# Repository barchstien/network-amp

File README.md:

# network-amp
PCB including DAC, audio amp, RaspberryPi interface and power supply

<br /><span xmlns:dct="http://purl.org/dc/terms/" property="dct:title">network-amp</span> by <span xmlns:cc="http://creativecommons.org/ns#" property="cc:attributionName">bastienauneau</span> is licensed under a <a rel="license" href="http://creativecommons.org/licenses/by-sa/4.0/">Creative Commons Attribution-ShareAlike 4.0 International License</a>.

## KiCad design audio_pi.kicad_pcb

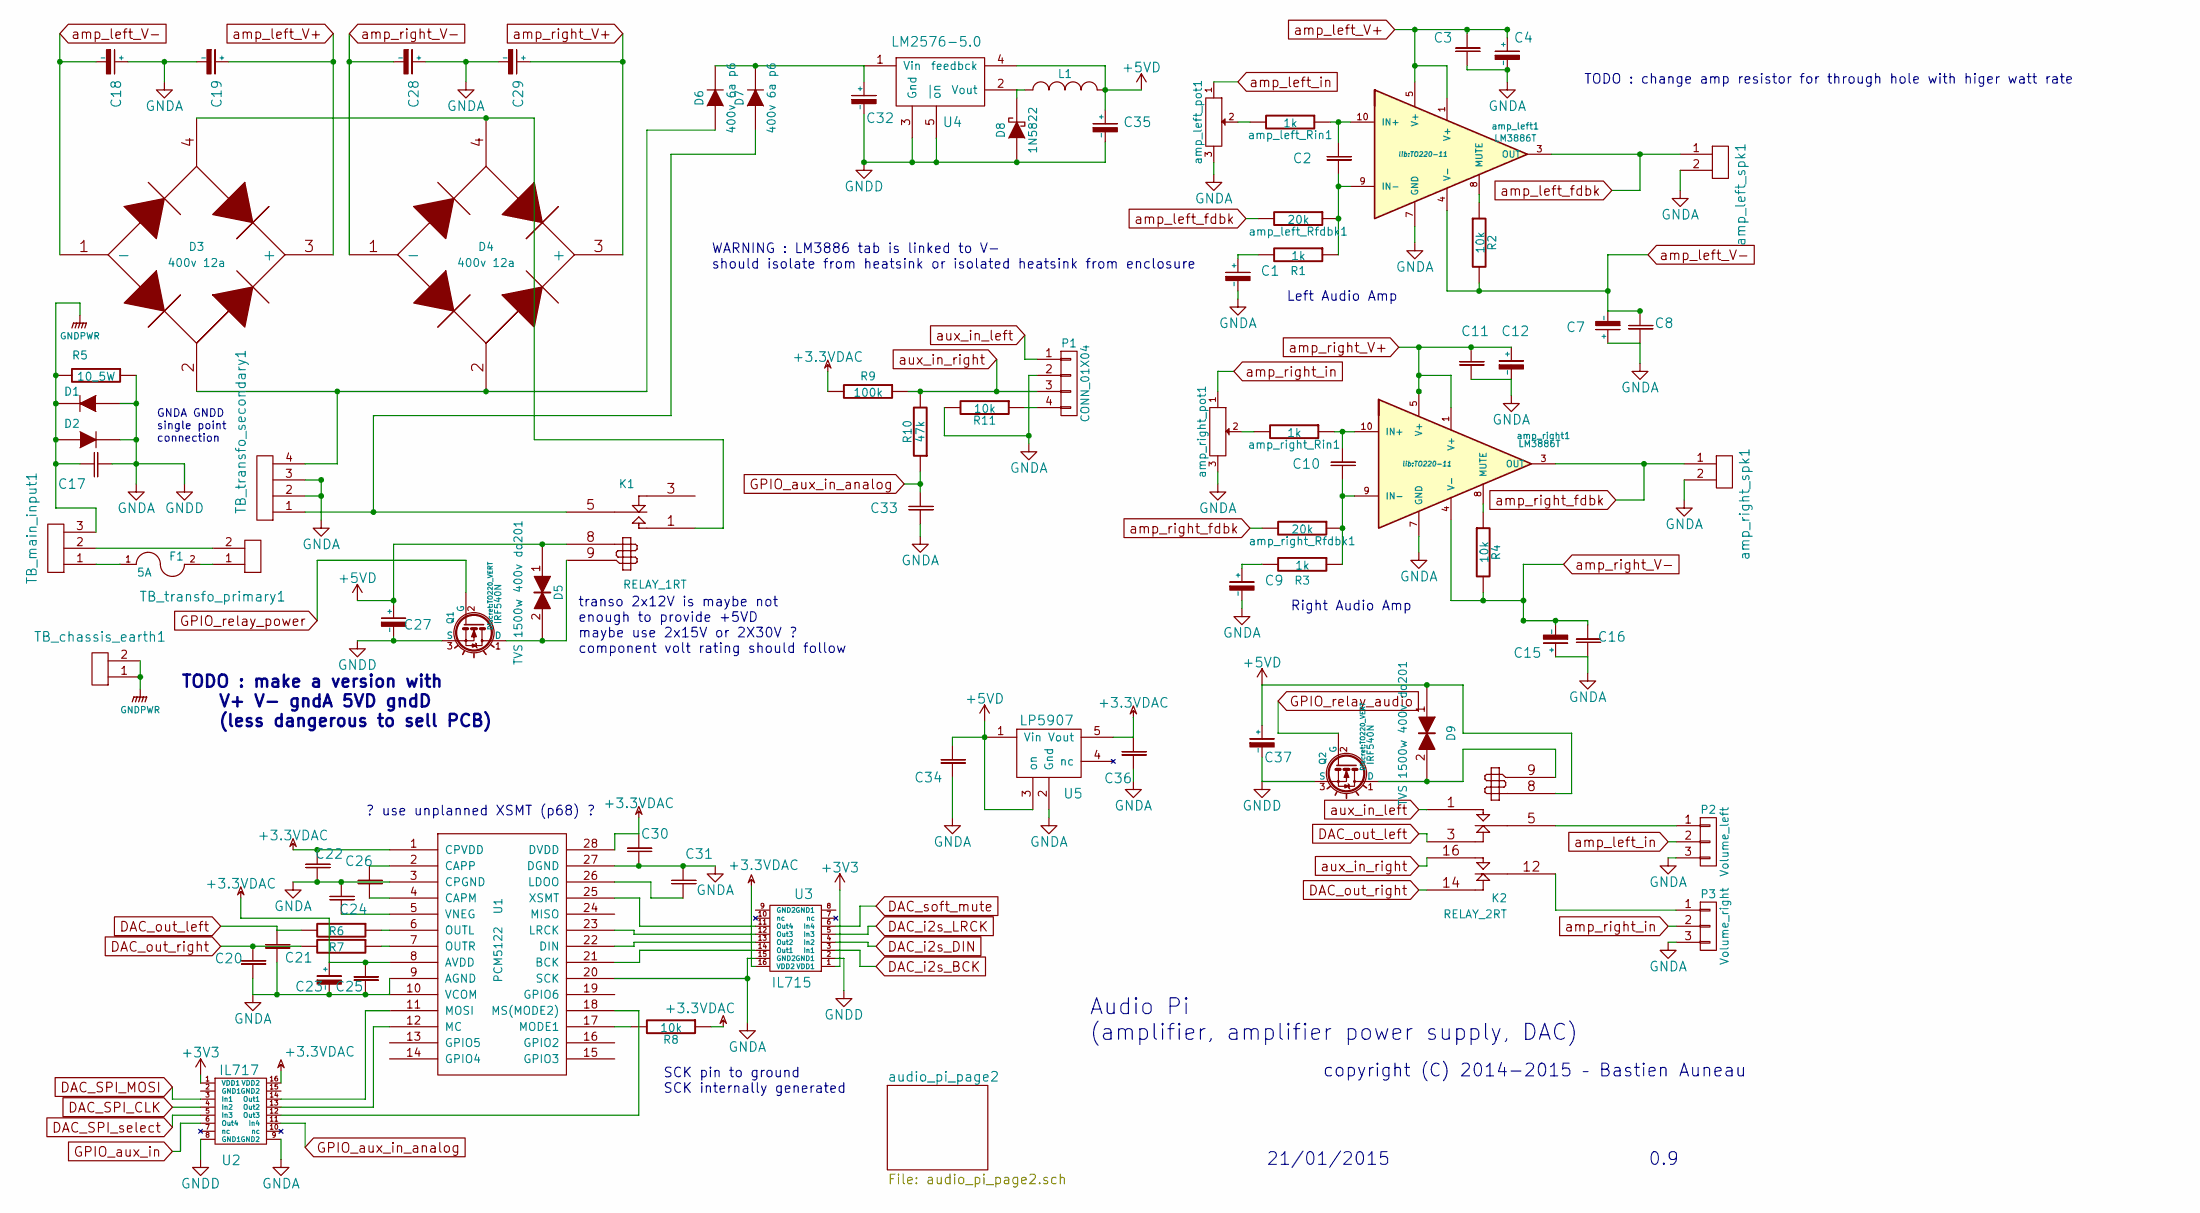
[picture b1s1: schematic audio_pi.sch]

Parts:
C1, C9: 22uf; Capacitor8x13RM3.8
C2, C10: 220pf; Capacitor6MMDiscRM5
C3, C8, C11, C16, C17: 100nf; Capacitor6MMDiscRM5
C4, C7, C12, C15, C23: 10uf; C1V7
C18, C19, C28, C29: 4700uF; Capacitor26x45RM10
C20, C21: 2.2nf; C_1206
C22, C25, C30, C31: 0.1uf; C_1206
C24, C26: 2.2uf; C_1206
C27, C32, C37: 100uf; Capacitor10x21RM5
C33: 10nf; C_1206
C34, C36: 1uf; C_1206
C35: 2200uf; Capacitor16x25RM7.5
D1, D2: 400v 6a p6; Diode_P600_Vertical_KathodeUp
D3, D4: 400v 12a; bornier4
D5, D9: TVS 1500w 400v do201; Diode_DO-41_SOD81_Horizontal_RM10
D6, D7: 400v 6a p6; Diode_P600_Horizontal
D8: 1N5822; Diode_DO-41_SOD81_Vertical_KathodeUp
F1: 5A; Fuseholder5x20_horiz_SemiClosed_Casing10x25mm
K1: RELAY_1RT; Relay_Power
K2: RELAY_2RT; Relais_double
L1: 100uH 5A; inductance
P1: CONN_01X04; Pin_Header_Straight_1x04
P2: Volume_left; Pin_Header_Straight_1x03
P3: Volume_right; Pin_Header_Straight_1x03
Q1, Q2: IRF540N; TO220_VERT
R1, R3: 1k; Resistor_Horizontal_RM10mm
R2, R4: 10k; Resistor_Horizontal_RM10mm
R5: 10_5W; Resistor_Horizontal_RM25mm
R6, R7: 470R; R_1206
R8, R11: 10k; R_1206
R9: 100k; R_1206
R10: 47k; R_1206
TB_chassis_earth1: Terminal_block_2; AK300-2
TB_main_input1: Terminal_block_3; AK300-3
TB_transfo_primary1: Terminal_block_2; AK300-2
TB_transfo_secondary1: Terminal_block_4; AK300-4
U1: PCM5122; TSSOP-28_4.4x9.7mm_Pitch0.65mm
U2: IL717; SOIC-16_3.9x9.9mm_Pitch1.27mm
U3: IL715; SOIC-16_3.9x9.9mm_Pitch1.27mm
U4: LM2576-5.0; Pentawatt_Neutral_Staggered_Verical_TO220-5-T05D
U5: LP5907; SOT-23-5
amp_left1: LM3886T; TO220-11
amp_left_Rfdbk1: 20k; Resistor_Horizontal_RM10mm
amp_left_Rin1: 1k; Resistor_Horizontal_RM10mm
amp_left_pot1: 10k; RV2X4
amp_left_spk1: Terminal_block_2; AK300-2
amp_right1: LM3886T; TO220-11
amp_right_Rfdbk1: 20k; Resistor_Horizontal_RM10mm
amp_right_Rin1: 1k; Resistor_Horizontal_RM10mm
amp_right_pot1: 10k; RV2X4
amp_right_spk1: Terminal_block_2; AK300-2

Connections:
+3.3VDAC: C22.2, C23.1 (+), C25.2, C30.2, C36.2, R8.1, R9.2, U1.1 (CPVDD), U1.8 (AVDD), U1.28 (DVDD), U2.16 (VDD2), U3.16 (VDD2), U5.5 (Vout)
+3V3: U2.1 (VDD1), U3.1 (VDD1); also elsewhere on the board
+5VD: C27.1 (+), C34.2, C35.1 (+), C37.1 (+), D5.1, D9.1, K1.8, K2.8, L1.2, U4.4 (feedbck), U5.1 (Vin), U5.3 (on); also elsewhere on the board
DAC_SPI_CLK: U2.4 (In2); also elsewhere on the board
DAC_SPI_select: U2.5 (In3); also elsewhere on the board
DAC_i2s_BCK: U3.3 (In1); also elsewhere on the board
DAC_i2s_DIN: U3.4 (In2); also elsewhere on the board
DAC_i2s_LRCK: U3.5 (In3); also elsewhere on the board
DAC_out_left: C21.2, K2.3 (R1), R6.2
DAC_out_right: C20.2, K2.14 (R2), R7.2
DAC_soft_mute: U3.6 (In4); also elsewhere on the board
GNDD: C1.2 (-), C3.1, C4.2 (-), C7.1 (+), C8.1, C9.2 (-), C11.1, C12.2 (-), C15.1 (+), C16.1, C17.2, C18.1 (+), C19.2 (-), C20.1, C21.1, C22.1, C23.2 (-), C24.2, C25.1, C27.2 (-), C28.1 (+), C29.2 (-), C30.1, C31.2, C32.2 (-), C33.1, C34.1, C35.2 (-), C36.1, C37.2 (-), D1.1 (A), D2.2 (K), D8.1 (A), P1.2, P2.3, P3.3, Q1.3 (S), Q2.3 (S), R5.1, R11.2, TB_transfo_secondary1.2, TB_transfo_secondary1.3, U1.3 (CPGND), U1.9 (AGND), U1.10 (VCOM), U1.20 (SCK), U1.27 (DGND), U2.8 (GND1), U2.9 (GND2), U3.2 (GND1), U3.15 (GND2), U4.3 (Gnd), U4.5 (~on), U5.2 (Gnd), amp_left1.7 (GND), amp_left_pot1.3, amp_left_spk1.2, amp_right1.7 (GND), amp_right_pot1.3, amp_right_spk1.2; also elsewhere on the board
GNDPWR: C17.1, D1.2 (K), D2.1 (A), R5.2, TB_chassis_earth1.1, TB_chassis_earth1.2, TB_main_input1.3
GPIO_aux_in: U2.6 (Out4); also elsewhere on the board
GPIO_aux_in_analog: C33.2, R10.1, U2.11 (In4)
GPIO_relay_audio: Q2.2 (G); also elsewhere on the board
GPIO_relay_power: Q1.2 (G); also elsewhere on the board
unnamed: C1.1 (+), R1.2
unnamed: C2.1, R1.1, amp_left1.9 (IN-), amp_left_Rfdbk1.1
unnamed: C2.2, amp_left1.10 (IN+), amp_left_Rin1.1
unnamed: C9.1 (+), R3.2
unnamed: C10.1, R3.1, amp_right1.9 (IN-), amp_right_Rfdbk1.1
unnamed: C10.2, amp_right1.10 (IN+), amp_right_Rin1.1
unnamed: C24.1, U1.5 (VNEG)
unnamed: C26.1, U1.4 (CAPM)
unnamed: C26.2, U1.2 (CAPP)
unnamed: C31.1, U1.26 (LDOO)
unnamed: C32.1 (+), D6.2 (K), D7.2 (K), U4.1 (Vin)
unnamed: D3.2, D4.2, D6.1 (A), TB_transfo_secondary1.4
unnamed: D3.4, D4.4, K1.1 (T1)
unnamed: D5.2, K1.9, Q1.1 (D)
unnamed: D7.1 (A), K1.5 (C1), TB_transfo_secondary1.1
unnamed: D8.2 (K), L1.1, U4.2 (Vout)
unnamed: D9.2, K2.9, Q2.1 (D)
unnamed: F1.1, TB_main_input1.1
unnamed: F1.2, TB_transfo_primary1.1
unnamed: K2.5 (C1), P2.1
unnamed: K2.12 (C2), P3.1
unnamed: P1.4, R11.1
unnamed: R2.1, amp_left1.8 (MUTE)
unnamed: R4.1, amp_right1.8 (MUTE)
unnamed: R6.1, U1.6 (OUTL)
unnamed: R7.1, U1.7 (OUTR)
unnamed: R8.2, U1.17 (MODE1)
unnamed: TB_main_input1.2, TB_transfo_primary1.2
unnamed: U1.11 (MOSI), U2.14 (Out1)
unnamed: U1.12 (MC), U2.13 (Out2)
unnamed: U1.18 (MS(MODE2)), U2.12 (Out3)
unnamed: U1.21 (BCK), U3.14 (Out1)
unnamed: U1.22 (DIN), U3.13 (Out2)
unnamed: U1.23 (LRCK), U3.12 (Out3)
unnamed: U1.25 (XSMT), U3.11 (Out4)
unnamed: amp_left_Rin1.2, amp_left_pot1.2
unnamed: amp_right_Rin1.2, amp_right_pot1.2
amp_left_V+: C3.2, C4.1 (+), C19.1 (+), D3.3 (+), amp_left1.1 (V+), amp_left1.5 (V+)
amp_left_V-: C7.2 (-), C8.2, C18.2 (-), D3.1 (-), R2.2, amp_left1.4 (V-)
amp_left_fdbk: amp_left1.3 (OUT), amp_left_Rfdbk1.2, amp_left_spk1.1
amp_left_in: P2.2, amp_left_pot1.1
amp_right_V+: C11.2, C12.1 (+), C29.1 (+), D4.3 (+), amp_right1.1 (V+), amp_right1.5 (V+)
amp_right_V-: C15.2 (-), C16.2, C28.2 (-), D4.1 (-), R4.2, amp_right1.4 (V-)
amp_right_fdbk: amp_right1.3 (OUT), amp_right_Rfdbk1.2, amp_right_spk1.1
amp_right_in: P3.2, amp_right_pot1.1
aux_in_left: K2.1 (T1), P1.1
aux_in_right: K2.16 (T2), P1.3, R9.1, R10.2
screen_SPI_MOSI: U2.3 (In1); also elsewhere on the board

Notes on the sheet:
Left Audio Amp
Right Audio Amp
Audio Pi (amplifier, amplifier power supply, DAC)
21/01/2015
0.9
copyright (C) 2014-2015 – Bastien Auneau
transo 2x12V is maybe not enough to provide +5VD maybe use 2x15V or 2X30V ? component volt rating should follow
GNDA GNDD single point connection
WARNING : LM3886 tab is linked to V- should isolate from heatsink or isolated heatsink from enclosure
SCK pin to ground SCK internally generated
? use unplanned XSMT (p68) ?
TODO : make a version with V+ V- gndA 5VD gndD (less dangerous to sell PCB)
TODO : change amp resistor for through hole with higer watt rate

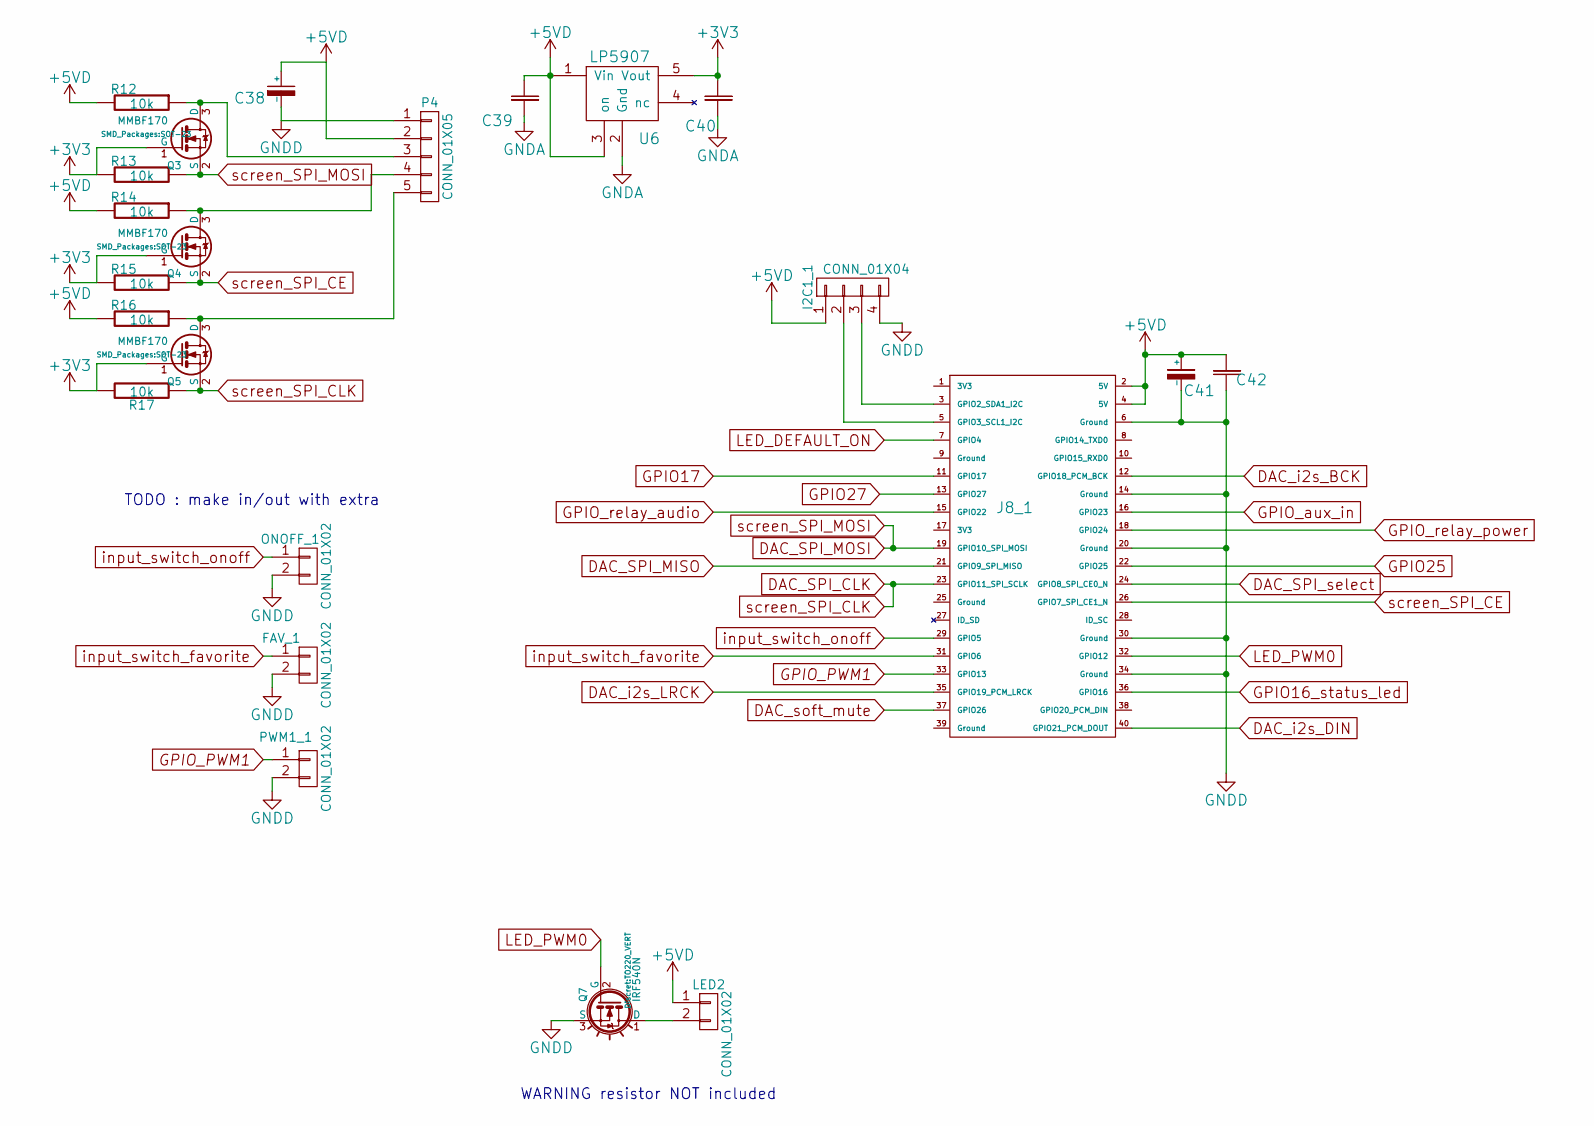
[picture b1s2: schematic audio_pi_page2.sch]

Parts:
C38: 10uf; C1V7
C39, C40: 1uf; R_1206
C41: 100uf; Capacitor10x21RM5
C42: 100nf; C_1206
FAV_1: CONN_01X02; Pin_Header_Straight_1x02
I2C1_1: CONN_01X04; Pin_Header_Straight_1x04
J8_1: RPI_B+_J8_header; Pin_Header_Straight_2x20
LED2: CONN_01X02; Pin_Header_Straight_1x02
ONOFF_1: CONN_01X02; Pin_Header_Straight_1x02
P4: CONN_01X05; Pin_Header_Straight_1x05
PWM1_1: CONN_01X02; Pin_Header_Straight_1x02
Q3, Q4, Q5: MMBF170; SOT-23
Q7: IRF540N; TO220_VERT
R12, R13, R14, R15, R16, R17: 10k; R_1206
U6: LP5907; SOT-23-5

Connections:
+3V3: C40.2, Q3.1 (G), Q4.1 (G), Q5.1 (G), R13.2, R15.2, R17.2, U6.5 (Vout); also elsewhere on the board
+5VD: C38.1 (+), C39.2, C41.1 (+), C42.2, I2C1_1.1, J8_1.2 (5V), J8_1.4 (5V), LED2.1, P4.2, R12.2, R14.2, R16.2, U6.1 (Vin), U6.3 (on); also elsewhere on the board
DAC_SPI_CLK: J8_1.23 (GPIO11_SPI_SCLK), Q5.2 (S), R17.1; also elsewhere on the board
DAC_SPI_MISO: J8_1.21 (GPIO9_SPI_MISO)
DAC_SPI_select: J8_1.24 (GPIO8_SPI_CE0_N); also elsewhere on the board
DAC_i2s_BCK: J8_1.12 (GPIO18_PCM_BCK); also elsewhere on the board
DAC_i2s_DIN: J8_1.40 (GPIO21_PCM_DOUT); also elsewhere on the board
DAC_i2s_LRCK: J8_1.35 (GPIO19_PCM_LRCK); also elsewhere on the board
DAC_soft_mute: J8_1.37 (GPIO26); also elsewhere on the board
GNDD: C38.2 (-), C39.1, C40.1, C41.2 (-), C42.1, FAV_1.2, I2C1_1.4, J8_1.6 (Ground), J8_1.14 (Ground), J8_1.20 (Ground), J8_1.30 (Ground), J8_1.34 (Ground), ONOFF_1.2, P4.1, PWM1_1.2, Q7.3 (S), U6.2 (Gnd); also elsewhere on the board
GPIO16_status_led: J8_1.36 (GPIO16)
GPIO17: J8_1.11 (GPIO17)
GPIO25: J8_1.22 (GPIO25)
GPIO27: J8_1.13 (GPIO27)
GPIO_PWM1: J8_1.33 (GPIO13), PWM1_1.1
GPIO_aux_in: J8_1.16 (GPIO23); also elsewhere on the board
GPIO_relay_audio: J8_1.15 (GPIO22); also elsewhere on the board
GPIO_relay_power: J8_1.18 (GPIO24); also elsewhere on the board
LED_DEFAULT_ON: J8_1.7 (GPIO4)
LED_PWM0: J8_1.32 (GPIO12), Q7.2 (G)
unnamed: I2C1_1.2, J8_1.5 (GPIO3_SCL1_I2C)
unnamed: I2C1_1.3, J8_1.3 (GPIO2_SDA1_I2C)
unnamed: LED2.2, Q7.1 (D)
unnamed: P4.3, Q3.3 (D), R12.1
unnamed: P4.4, Q4.3 (D), R14.1
unnamed: P4.5, Q5.3 (D), R16.1
input_switch_favorite: FAV_1.1, J8_1.31 (GPIO6)
input_switch_onoff: J8_1.29 (GPIO5), ONOFF_1.1
screen_SPI_CE: J8_1.26 (GPIO7_SPI_CE1_N), Q4.2 (S), R15.1
screen_SPI_MOSI: J8_1.19 (GPIO10_SPI_MOSI), Q3.2 (S), R13.1; also elsewhere on the board

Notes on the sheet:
TODO : make in/out with extra
WARNING resistor NOT included

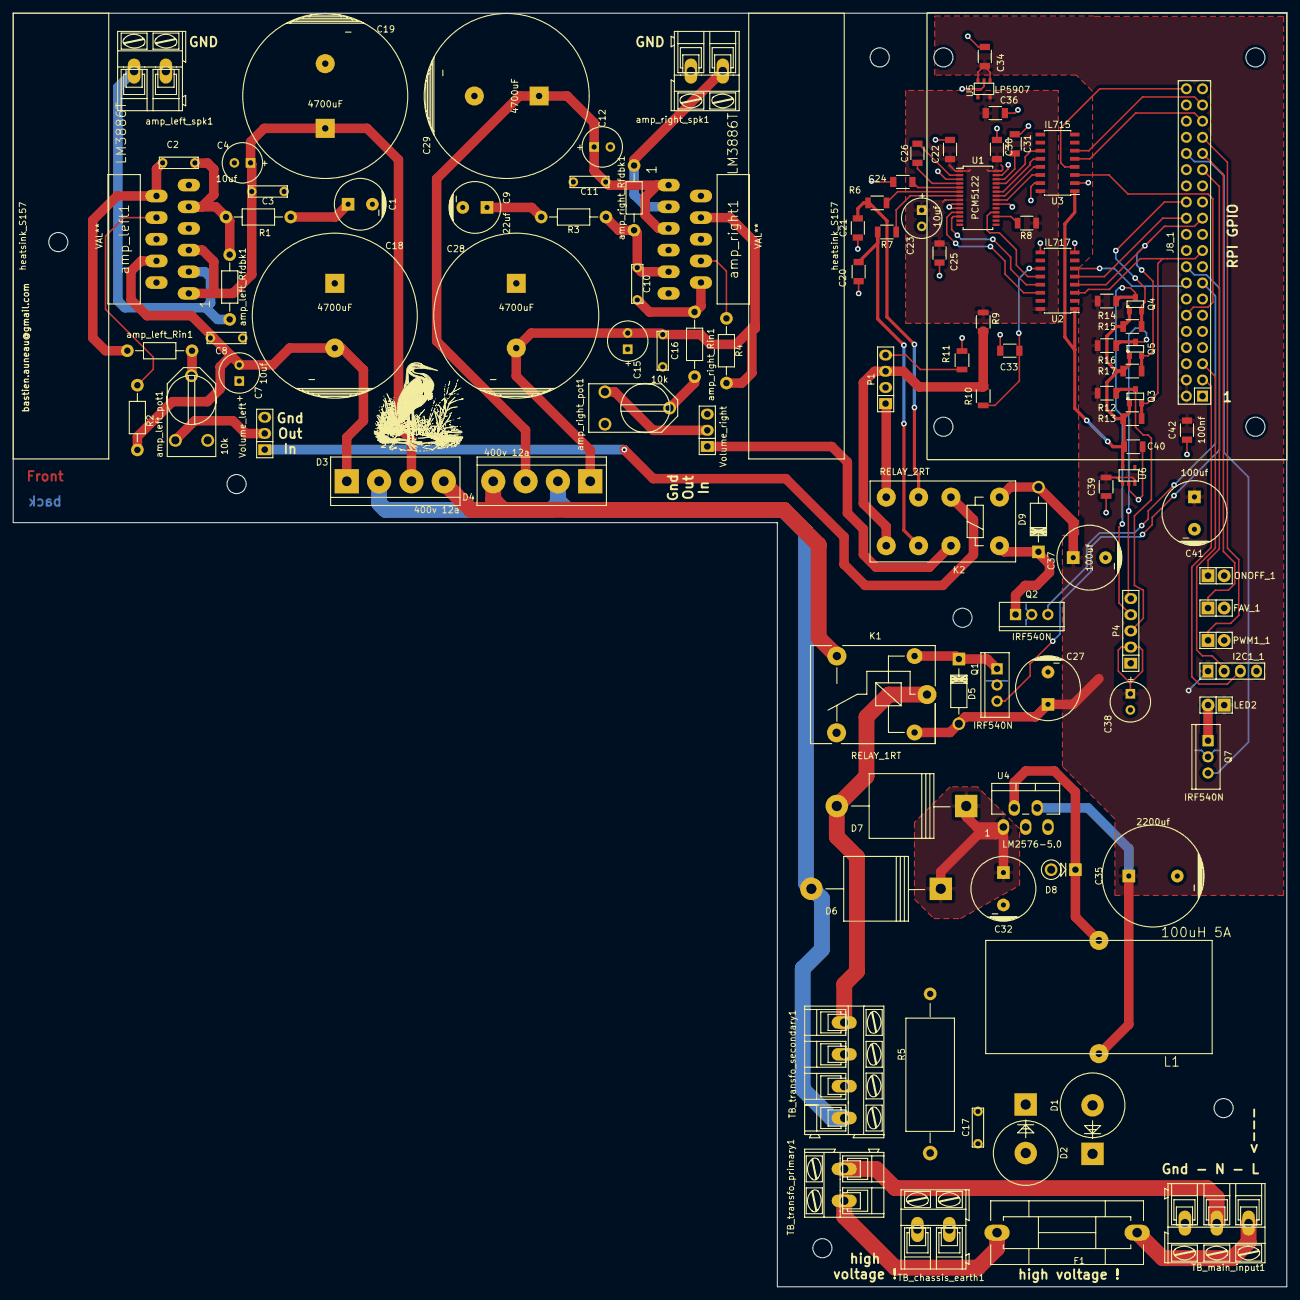
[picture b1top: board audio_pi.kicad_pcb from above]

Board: 2 copper layers, 200.0 x 200.0 mm, 116 parts (0 on the bottom side), 76 nets.

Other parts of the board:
MountingHole_3mm, MountingHole_3mm#2, MountingHole_3mm#3, MountingHole_3mm#4, MountingHole_3mm#5, MountingHole_3mm#6, MountingHole_3mm#7, MountingHole_3mm#8, MountingHole_3mm#9, MountingHole_3mm#10: VAL**; MountingHole_3mm
heatsink_S157, heatsink_S157#2: VAL**; heatsink_S157

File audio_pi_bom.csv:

Reference, Value, Footprint, Datasheet, e44.com, SUPPLIER, SUPPLIER PART NO., Comment
amp_left1,LM3886T,lib:TO220-11,,LM3886T,,,
U1,PCM5122,Housings_SSOP:TSSOP-28_4.4x9.7mm_Pitch0.65mm,,,Farnell,2307931,
R2,10k,Resistors_ThroughHole:Resistor_Horizontal_RM10mm,,MA10K0,,,
C8,100nf,Capacitors_ThroughHole:Capacitor6MMDiscRM5,,CC5100NF,,,
C3,100nf,Capacitors_ThroughHole:Capacitor6MMDiscRM5,,CC5100NF,,,
C4,10uf,Discret:C1V7,,CHR10100,,,
C7,10uf,Discret:C1V7,,CHR10100,,,
amp_left_pot1,10k,Discret:RV2X4,,CA9V10K,,,
amp_left_spk1,Terminal_block_2,Connect:AK300-2,,SCREW02BL,,,
C2,220pf,Capacitors_ThroughHole:Capacitor6MMDiscRM5,,CC5220PF/500,,,
R1,1k,Resistors_ThroughHole:Resistor_Horizontal_RM10mm,,MA1K0,,,
amp_left_Rfdbk1,20k,Resistors_ThroughHole:Resistor_Horizontal_RM10mm,,MA20K0,,,
amp_left_Rin1,1k,Resistors_ThroughHole:Resistor_Horizontal_RM10mm,,MA1K0,,,
R4,10k,Resistors_ThroughHole:Resistor_Horizontal_RM10mm,,MA10K0,,,
C16,100nf,Capacitors_ThroughHole:Capacitor6MMDiscRM5,,CC5100NF,,,
C11,100nf,Capacitors_ThroughHole:Capacitor6MMDiscRM5,,CC5100NF,,,
C15,10uf,Discret:C1V7,,CHR10100,,,
amp_right_pot1,10k,Discret:RV2X4,,CA9V10K,,,
amp_right_spk1,Terminal_block_2,Connect:AK300-2,,SCREW02BL,,,
C10,220pf,Capacitors_ThroughHole:Capacitor6MMDiscRM5,,CC5220PF/500,,,
R3,1k,Resistors_ThroughHole:Resistor_Horizontal_RM10mm,,MA1K0,,,
amp_right_Rfdbk1,20k,Resistors_ThroughHole:Resistor_Horizontal_RM10mm,,MA20K0,,,
amp_right_Rin1,1k,Resistors_ThroughHole:Resistor_Horizontal_RM10mm,,MA1K0,,,
TB_main_input1,Terminal_block_3,Connect:AK300-3,,SCREW03BL,,,
C17,100nf,Capacitors_ThroughHole:Capacitor6MMDiscRM5,,CCM100NF,,,
D2,400v 6a p6,Diodes_ThroughHole:Diode_P600_Vertical_KathodeUp,,P600G,,,
D1,400v 6a p6,Diodes_ThroughHole:Diode_P600_Vertical_KathodeUp,,P600G,,,
R5,10_5W,Resistors_ThroughHole:Resistor_Horizontal_RM25mm,,vrac,,,
TB_transfo_primary1,Terminal_block_2,Connect:AK300-2,,SCREW02BL,,,
TB_transfo_secondary1,Terminal_block_4,Connect:AK300-4,,2xSCREW02BL,,,
D4,400v 12a,Connect:bornier4,,KBU12G,,,
D3,400v 12a,Connect:bornier4,,KBU12G,,,
C18,4700uF,Capacitors_ThroughHole:Capacitor26x45RM10,,CHR470080-85,,,
C28,4700uF,Capacitors_ThroughHole:Capacitor26x45RM10,,CHR470080-85,,,
C19,4700uF,Capacitors_ThroughHole:Capacitor26x45RM10,,CHR470080-85,,,
C29,4700uF,Capacitors_ThroughHole:Capacitor26x45RM10,,CHR470080-85,,,
U4,LM2576-5.0,Pentawatts:Pentawatt_Neutral_Staggered_Verical_TO220-5-T05D,,LM2576T5,,,
C32,100uf,Capacitors_ThroughHole:Capacitor10x21RM5,,CHR100100,,,
D8,1N5822,Diodes_ThroughHole:Diode_DO-41_SOD81_Vertical_KathodeUp,,1N5822,,,
C35,2200uf,Capacitors_ThroughHole:Capacitor16x25RM7.5,,CHR220035,,,
L1,100uH 5A,lib:inductance,,HFSECO5/100,,,
U5,LP5907,SMD_Packages:SOT-23-5,,,Digikey,296-38557-1-ND,
K2,RELAY_2RT,lib:Relais_double,,F3022-5,,,
K1,RELAY_1RT,lib:Relay_Power,,F3611-5,,,
Q1,IRF540N,Discret:TO220_VERT,,IRF540NPBF,,,
Q2,IRF540N,Discret:TO220_VERT,,IRF540NPBF,,,
P2,Volume_left,Pin_Headers:Pin_Header_Straight_1x03,,BTWM3,,,
P3,Volume_right,Pin_Headers:Pin_Header_Straight_1x03,,BTWM3,,,
C37,100uf,Capacitors_ThroughHole:Capacitor10x21RM5,,CHR100100,,,
D9,TVS 1500w 400v do201,Diodes_ThroughHole:Diode_DO-41_SOD81_Horizontal_RM10,,1.5KE400CA,,,
D5,TVS 1500w 400v do201,Diodes_ThroughHole:Diode_DO-41_SOD81_Horizontal_RM10,,1.5KE400CA,,,
C27,100uf,Capacitors_ThroughHole:Capacitor10x21RM5,,CHR100100,,,
D6,400v 6a p6,Diodes_ThroughHole:Diode_P600_Horizontal,,P600G,,,
D7,400v 6a p6,Diodes_ThroughHole:Diode_P600_Horizontal,,P600G,,,
F1,5A,Fuse_Holders_and_Fuses:Fuseholder5x20_horiz_SemiClosed_Casing10x25mm,,FUSE/HL*,,,
TB_chassis_earth1,Terminal_block_2,Connect:AK300-2,,SCREW02BL,,,
C22,0.1uf,Capacitors_SMD:C_1206,,,Farnell,1759361,PCB Train free component stock
C34,1uf,Capacitors_SMD:C_1206,,,Farnell,1759454,PCB Train free component stock
C26,2.2uf,Capacitors_SMD:C_1206,,,Farnell,2310423,PCB Train free component stock
C24,2.2uf,Capacitors_SMD:C_1206,,,Farnell,2310423,PCB Train free component stock
R6,470R,Resistors_SMD:R_1206,,,Farnell,2129621,PCB Train free component stock
R7,470R,Resistors_SMD:R_1206,,,Farnell,2129621,PCB Train free component stock
C20,2.2nf,Capacitors_SMD:C_1206,,,Farnell,1759341,PCB Train free component stock
C23,10uf,Discret:C1V7,,CHR10100,,,
C30,0.1uf,Capacitors_SMD:C_1206,,,Farnell,1759361,PCB Train free component stock
C31,0.1uf,Capacitors_SMD:C_1206,,,Farnell,1759361,PCB Train free component stock
R8,10k,Resistors_SMD:R_1206,,,Farnell,2129728,PCB Train free component stock
U2,IL717,Housings_SOIC:SOIC-16_3.9x9.9mm_Pitch1.27mm,,,Farnell,9570659,
P1,CONN_01X04,Pin_Headers:Pin_Header_Straight_1x04,,header pin,,,
R10,47k,Resistors_SMD:R_1206,,,Farnell,2129783,PCB Train free component stock
R9,100k,Resistors_SMD:R_1206,,,Farnell,2129810,PCB Train free component stock
R11,10k,Resistors_SMD:R_1206,,,Farnell,2129728,PCB Train free component stock
C33,10nf,Capacitors_SMD:C_1206,,,Farnell,1759350,PCB Train free component stock
C12,10uf,Discret:C1V7,,CHR10100,,,
C36,1uf,Capacitors_SMD:C_1206,,,Farnell,1759454,PCB Train free component stock
C25,0.1uf,Capacitors_SMD:C_1206,,,Farnell,1759361,PCB Train free component stock
C21,2.2nf,Capacitors_SMD:C_1206,,,Farnell,1759341,PCB Train free component stock
U3,IL715,Housings_SOIC:SOIC-16_3.9x9.9mm_Pitch1.27mm,,,Farnell,9570632,
amp_right1,LM3886T,lib:TO220-11,,LM3886T,,,
C9,22uf,Capacitors_ThroughHole:Capacitor8x13RM3.8,,CHR22100,,,
C1,22uf,Capacitors_ThroughHole:Capacitor8x13RM3.8,,CHR22100,,,
Q3,MMBF170,SMD_Packages:SOT-23,,,Farnell,9845399,
Q4,MMBF170,SMD_Packages:SOT-23,,,Farnell,9845399,
Q5,MMBF170,SMD_Packages:SOT-23,,,Farnell,9845399,
R12,10k,Resistors_SMD:R_1206,,,Farnell,2129728,PCB Train free component stock
R13,10k,Resistors_SMD:R_1206,,,Farnell,2129728,PCB Train free component stock
R14,10k,Resistors_SMD:R_1206,,,Farnell,2129728,PCB Train free component stock
R15,10k,Resistors_SMD:R_1206,,,Farnell,2129728,PCB Train free component stock
R17,10k,Resistors_SMD:R_1206,,,Farnell,2129728,PCB Train free component stock
R16,10k,Resistors_SMD:R_1206,,,Farnell,2129728,PCB Train free component stock
C38,10uf,Discret:C1V7,,CHR10100,,,
FAV_1,CONN_01X02,Pin_Headers:Pin_Header_Straight_1x02,,BTWM2,,,
U6,LP5907,SMD_Packages:SOT-23-5,,,Digikey,296-38557-1-ND,
C39,1uf,Resistors_SMD:R_1206,,,Farnell,1759454,PCB Train free component stock
C40,1uf,Resistors_SMD:R_1206,,,Farnell,1759454,PCB Train free component stock
ONOFF_1,CONN_01X02,Pin_Headers:Pin_Header_Straight_1x02,,BTWM2,,,
J8_1,RPI_B+_J8_header,Pin_Headers:Pin_Header_Straight_2x20,
C41,100uf,Capacitors_ThroughHole:Capacitor10x21RM5,,CHR100100,,,
C42,100nf,Capacitors_SMD:C_1206,,,Farnell,1759361,PCB Train free component stock
PWM1_1,CONN_01X02,Pin_Headers:Pin_Header_Straight_1x02,,BTWM2,,,
Q7,IRF540N,Discret:TO220_VERT,,IRF540NPBF,,,
LED2,CONN_01X02,Pin_Headers:Pin_Header_Straight_1x02,,BTWM2,,,
P4,CONN_01X05,Pin_Headers:Pin_Header_Straight_1x05,
I2C1_1,CONN_01X04,Pin_Headers:Pin_Header_Straight_1x04,

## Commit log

2015-02-25 Update LICENSE
2015-02-25 first upload of project
2015-02-25 cleaned up, checked validity
